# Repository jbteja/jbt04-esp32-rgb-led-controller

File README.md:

# ESP Hub75 RGB Panel Controller
> Image of the board:

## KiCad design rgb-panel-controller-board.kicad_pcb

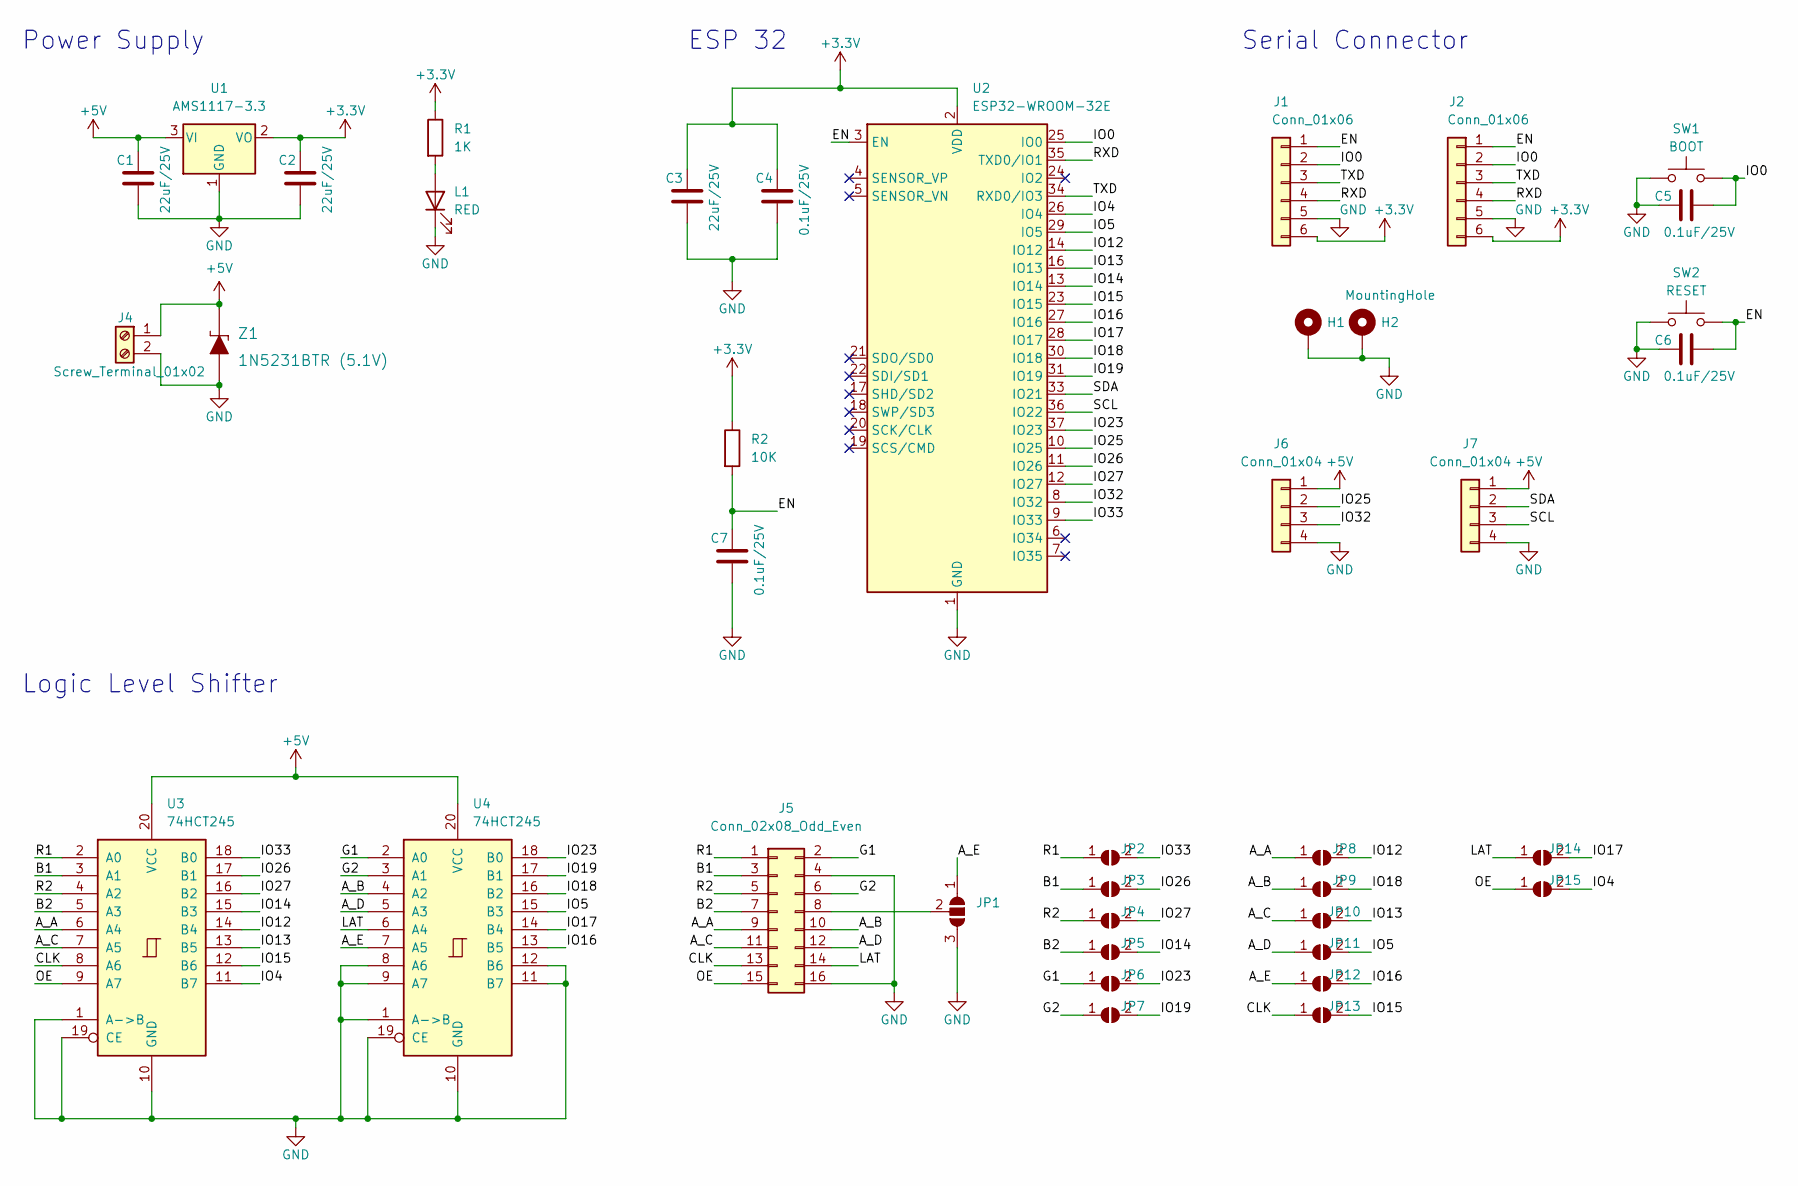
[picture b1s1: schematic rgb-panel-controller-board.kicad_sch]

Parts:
C1: 22uF/25V; CP_EIA-3528-21_Kemet-B_Pad1.50x2.35mm_HandSolder
C2, C3: 22uF/25V; C_0805_2012Metric
C4, C5, C6, C7: 0.1uF/25V; C_0805_2012Metric
H1, H2: MountingHole; MountingHole_3.2mm_M3_Pad
J1: Conn_01x06; JST_SH_BM06B-SRSS-TB_1x06-1MP_P1.00mm_Vertical
J2: Conn_01x06; PinHeader_1x06_P2.54mm_Vertical
J4: Screw_Terminal_01x02; TerminalBlock_Phoenix_PT-1,5-2-5.0-H_1x02_P5.00mm_Horizontal
J5: Conn_02x08_Odd_Even; IDC-Header_2x08_P2.54mm_Vertical
J6, J7: Conn_01x04; PinSocket_1x04_P2.54mm_Vertical
JP1: SolderJumper_3_Open; SolderJumper-3_P1.3mm_Open_RoundedPad1.0x1.5mm
JP2, JP3, JP4, JP5, JP6, JP7, JP8, JP9, JP10, JP11, JP12, JP13, JP14, JP15: SolderJumper_2_Open; R_0402_1005Metric_Pad0.72x0.64mm_HandSolder
L1: RED; LED_0805_2012Metric
R1: 1K; R_0805_2012Metric
R2: 10K; R_0805_2012Metric
SW1: BOOT; TACTILE_SWITCH_SMD_6.0X3.5MM
SW2: RESET; TACTILE_SWITCH_SMD_6.0X3.5MM
U1: AMS1117-3.3; SOT-223-3_TabPin2
U2: ESP32-WROOM-32E; ESP32-WROOM-32
U3, U4: 74HCT245; ETSSOP-20-1EP_4.4x6.5mm_P0.65mm_EP3x4.2mm
Z1: 1N5231BTR (5.1V); SOD-80; MPN 1N5231BTR; Digi-Key_PN 1N5231BFSCT-ND

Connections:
+3V3: C2.1, C3.1, C4.1, J1.6, J2.6, R1.1, R2.1, U1.2 (VO), U2.2 (VDD)
+5V: C1.1, J4.1, J6.1, J7.1, U1.3 (VI), U3.20 (VCC), U4.20 (VCC), Z1.K
/A_A: J5.9, JP8.1 (A), U3.6 (A4)
/A_B: J5.10, JP9.1 (A), U4.4 (A2)
/A_C: J5.11, JP10.1 (A), U3.7 (A5)
/A_D: J5.12, JP11.1 (A), U4.5 (A3)
/A_E: JP1.1 (A), JP12.1 (A), U4.7 (A5)
/B1: J5.3, JP3.1 (A), U3.3 (A1)
/B2: J5.7, JP5.1 (A), U3.5 (A3)
/CLK: J5.13, JP13.1 (A), U3.8 (A6)
/EN: C6.2, C7.1, J1.1, J2.1, R2.2, SW2.2, U2.3 (EN)
/G1: J5.2, JP6.1 (A), U4.2 (A0)
/G2: J5.6, JP7.1 (A), U4.3 (A1)
/IO0: C5.2, J1.2, J2.2, SW1.2, U2.25 (IO0)
/IO4: JP15.2 (B), U2.26 (IO4), U3.11 (B7)
/IO5: JP11.2 (B), U2.29 (IO5), U4.15 (B3)
/IO12: JP8.2 (B), U2.14 (IO12), U3.14 (B4)
/IO13: JP10.2 (B), U2.16 (IO13), U3.13 (B5)
/IO14: JP5.2 (B), U2.13 (IO14), U3.15 (B3)
/IO15: JP13.2 (B), U2.23 (IO15), U3.12 (B6)
/IO16: JP12.2 (B), U2.27 (IO16), U4.13 (B5)
/IO17: JP14.2 (B), U2.28 (IO17), U4.14 (B4)
/IO18: JP9.2 (B), U2.30 (IO18), U4.16 (B2)
/IO19: JP7.2 (B), U2.31 (IO19), U4.17 (B1)
/IO23: JP6.2 (B), U2.37 (IO23), U4.18 (B0)
/IO25: J6.2, U2.10 (IO25)
/IO26: JP3.2 (B), U2.11 (IO26), U3.17 (B1)
/IO27: JP4.2 (B), U2.12 (IO27), U3.16 (B2)
/IO32: J6.3, U2.8 (IO32)
/IO33: JP2.2 (B), U2.9 (IO33), U3.18 (B0)
/LAT: J5.14, JP14.1 (A), U4.6 (A4)
/OE: J5.15, JP15.1 (A), U3.9 (A7)
/R1: J5.1, JP2.1 (A), U3.2 (A0)
/R2: J5.5, JP4.1 (A), U3.4 (A2)
/RXD: J1.4, J2.4, U2.35 (TXD0/IO1)
/SCL: J7.3, U2.36 (IO22)
/SDA: J7.2, U2.33 (IO21)
/TXD: J1.3, J2.3, U2.34 (RXD0/IO3)
GND: C1.2, C2.2, C3.2, C4.2, C5.1, C6.1, C7.2, H1.1, H2.1, J1.5, J2.5, J4.2, J5.4, J5.16, J6.4, J7.4, JP1.3 (B), L1.1 (K), SW1.1, SW2.1, U1.1 (GND), U2.1 (GND), U2.15 (GND), U2.38 (GND), U2.39 (GND), U3.1 (A->B), U3.10 (GND), U3.19 (CE), U4.1 (A->B), U4.8 (A6), U4.9 (A7), U4.10 (GND), U4.11 (B7), U4.12 (B6), U4.19 (CE), Z1.A
unnamed: J5.8, JP1.2 (C)
unnamed: L1.2 (A), R1.2

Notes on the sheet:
Logic Level Shifter
Serial Connector
ESP 32
Power Supply

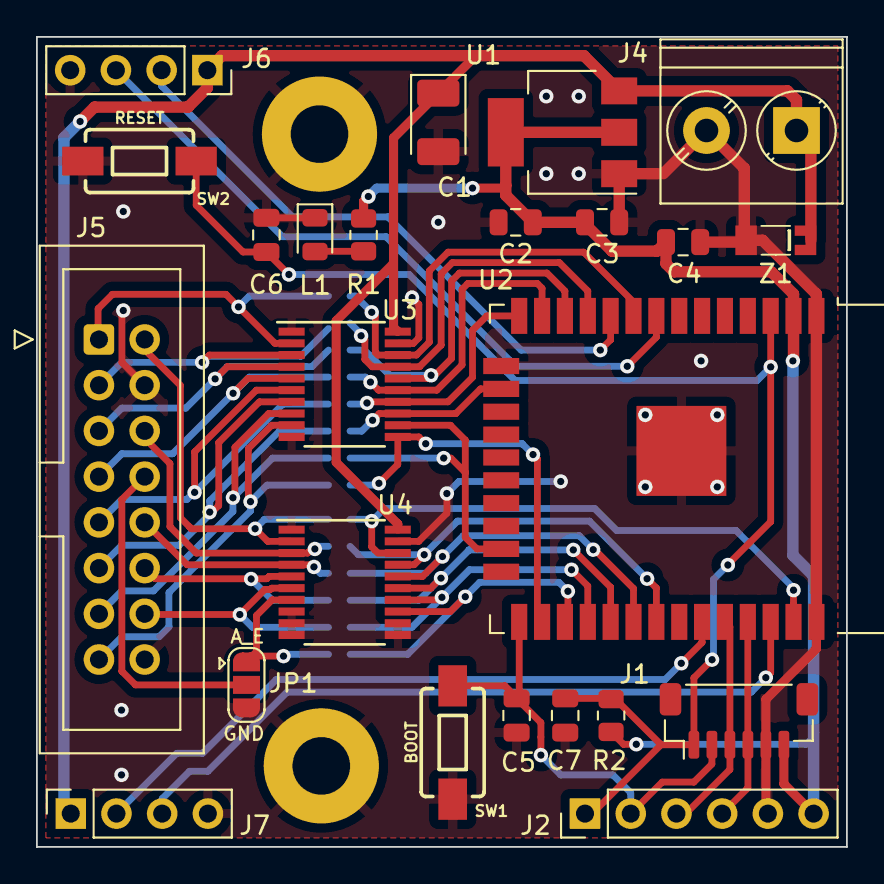
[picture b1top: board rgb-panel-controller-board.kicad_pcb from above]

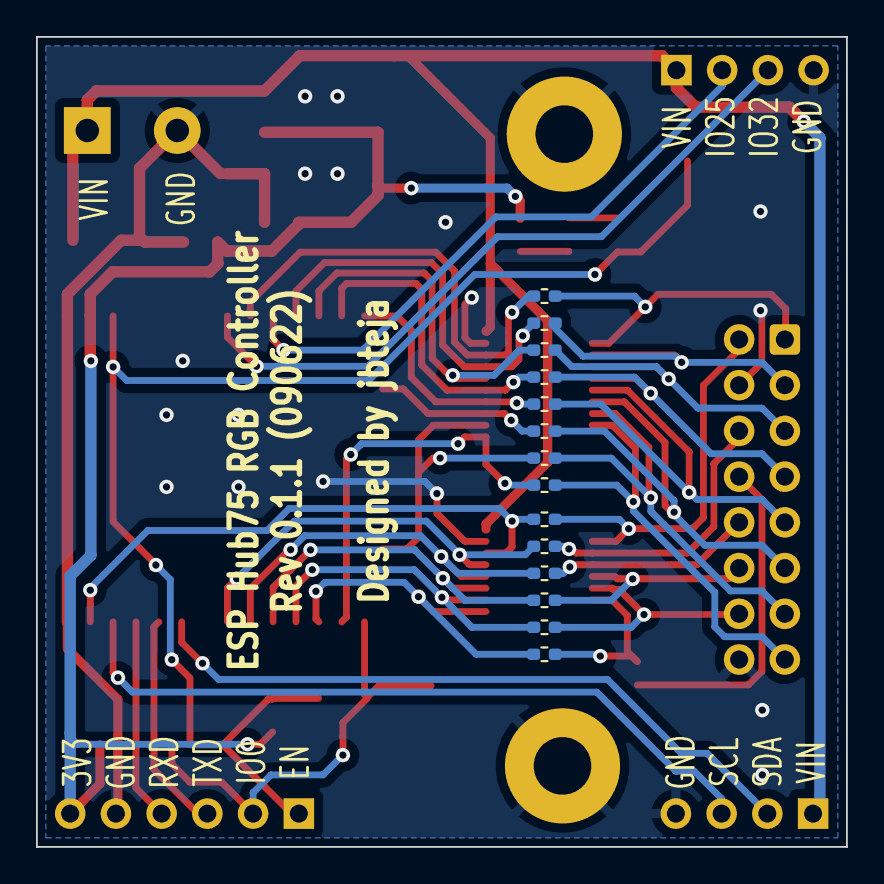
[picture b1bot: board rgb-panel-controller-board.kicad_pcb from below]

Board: 2 copper layers, 45.0 x 45.0 mm, 40 parts (14 on the bottom side), 41 nets.

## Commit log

2022-06-11 All changes related of rev 0.2.0
2022-06-11 Updated readme to rev 0.2.0
2022-06-11 Updated typo in readme
2023-06-14 Updating ignore and license file
